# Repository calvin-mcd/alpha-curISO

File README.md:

# Alpha CurISO

The Alpha CurISO is a community pcb for the [Curio](https://mechvault.net/products/group-buy-curio-40-keyboard-kit). It supports two different Alpha Staggers and Ortho Layouts.
This is a collaboration between jade_themaid, airuei, galvy0 and calvin.

## Layout

## Todo

- [ ] order pcb, plates
- [ ] create firmware
- [ ] test pcb in case

## Disclaimer

Please note that this project is a work in progress with no guarantees of a working outcome. No-one involved in this project is responsible for any usage issues that may arise. However, feel free to edit, modify and otherwise utilise these files.

## License

Shield: 

This work is licensed under a  
[Creative Commons Attribution-NonCommercial-ShareAlike 4.0 International License](http://creativecommons.org/licenses/by-nc-sa/4.0/).

## Credits

As always big thanks also to the many people who inspired and helped with this board!

Any questions, contact Calvin0563 on Discord.

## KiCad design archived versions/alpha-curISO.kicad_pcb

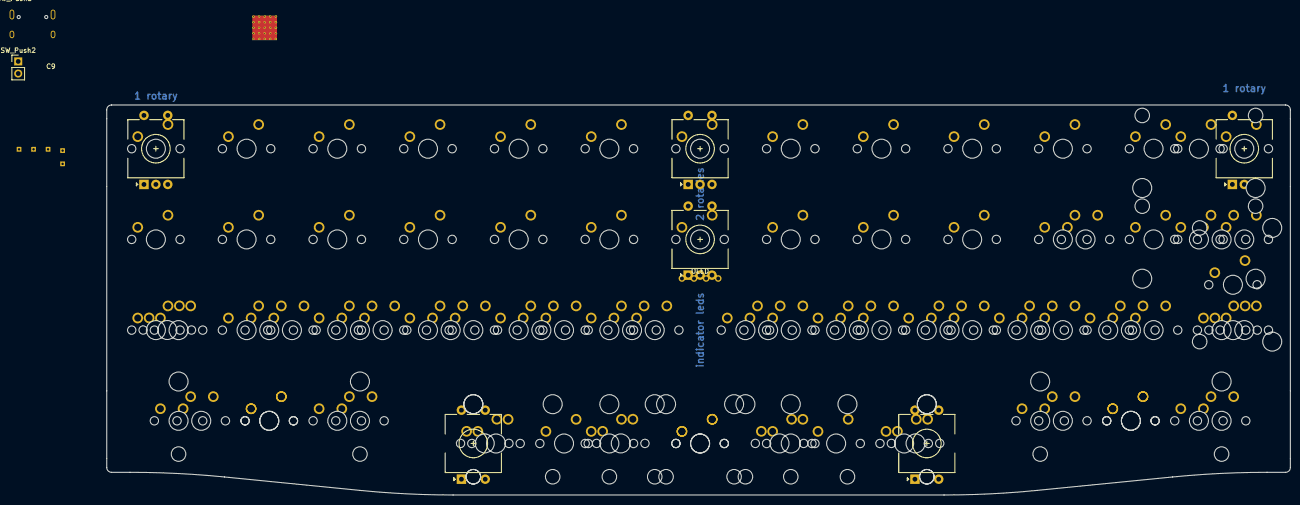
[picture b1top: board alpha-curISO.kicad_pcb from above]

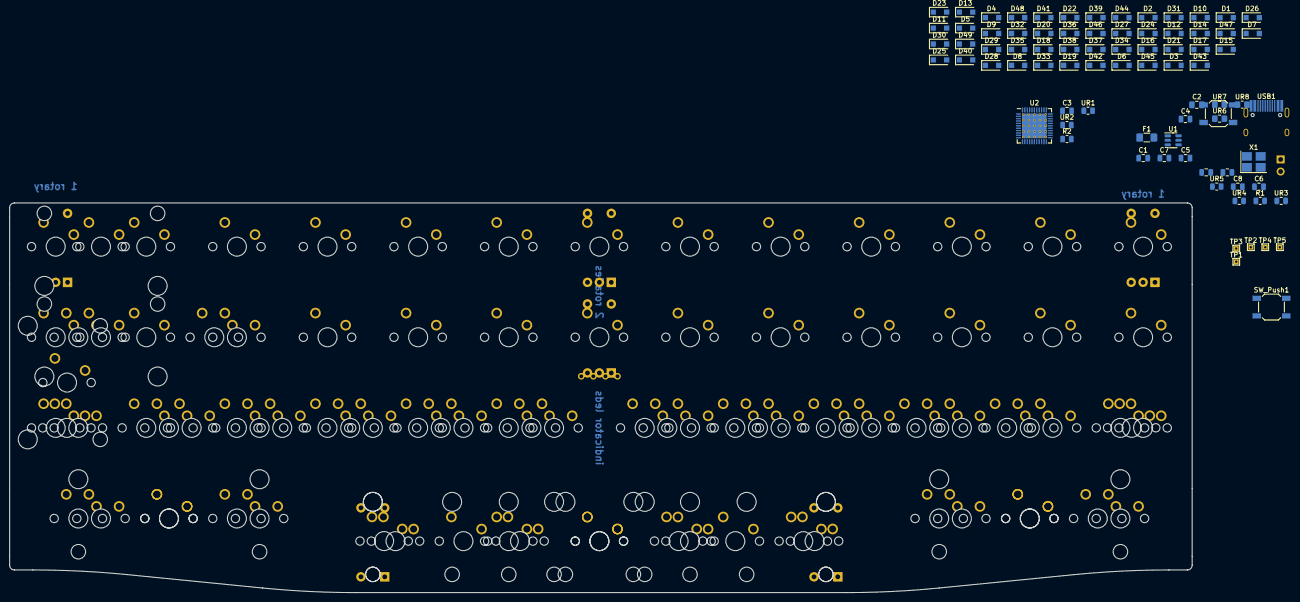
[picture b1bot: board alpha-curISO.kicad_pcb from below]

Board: 2 copper layers, 248.6 x 81.9 mm, 180 parts (81 on the bottom side), 83 nets, no tracks yet.

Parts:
C1: 4.7uF; C_0805_2012Metric
C2: 2.2uF; C_0805_2012Metric_Pad1.18x1.45mm_HandSolder
C3: 1uf; C_0805_2012Metric
C4: 10uF; C_0805_2012Metric
C5, C6, C7, C8: 0.1uf; C_0805_2012Metric
C9, C10: 22p; C_0805_2012Metric
D1, D2, D3, D4, D5, D6, D7, D8, D9, D10, D11, D12, D13, D14, D15, D16, D17, D18, D19, D20, D21, D22, D23, D24, D25, D26, D27, D28, D29, D30, D31, D32, D33, D34, D35, D36, D37, D38, D39, D40, D41, D42, D43, D44, D45, D46, D47, D48, D49: D_Small; D_SOD-123F
F1: Polyfuse_Small; Fuse_1206_3216Metric_Pad1.42x1.75mm_HandSolder
OL1: OLED; OLED_v2
R1, R2: 10k; R_0805_2012Metric
SW1, SW2, SW3, SW4, SW5, SW6, SW7, SW8, SW9, SW10, SW11, SW12, SW13, SW14, SW15, SW16, SW17, SW18, SW19, SW20, SW21, SW22, SW23, SW24, SW25, SW26, SW27(ortho)1, SW28, SW28(1.5stagger)1, SW28(ortho)1, SW29, SW29(1.5stagger)1, SW29(ortho)1, SW30, SW30(1.5stagger)1, SW30(ortho)1, SW31, SW31(1.5stagger)1, SW31(ortho)1, SW32, SW32(1.5stagger)1, SW32(ortho)1, SW33, SW33(1.5stagger)1, SW33(ortho)1, SW34, SW34(1.5stagger)1, SW34(ortho)1, SW35, SW35(1.5stagger)1, SW35(ortho)1, SW36, SW36(1.5stagger)1, SW36(ortho)1, SW37, SW37(1.5stagger)1, SW37(ortho)1, SW38(ortho)1, SW39, SW40, SW41, SW47, SW48, SW49: SW_Push_45deg; MXOnly-1U-NoLED
SW12(2)1, SW26(2)1: SW_Push_45deg; MXOnly-2U-NoLED
SW24(1.5)1, SW25(1.5)1, SW27(1.5)1, SW38(1.5)1, SW39(1.5)1, SW41(1.5)1, SW42(1.5)1, SW46(1.5)1, SW47(1.5)1, SW49(1.5)1: SW_Push_45deg; MXOnly-1.5U-NoLED
SW26(ISO)1: SW_Push_45deg; MXOnly-ISO-NoLED
SW27(1.25)1, SW38(1.25)1, SW42(1.25)1, SW46(1.25)1: SW_Push_45deg; MXOnly-1.25U-NoLED
SW40(3)1, SW42(3)1, SW44(3)1, SW46(3)1, SW48(3)1: SW_Push_45deg; MXOnly-3U-ReversedStabilizers-NoLED
SW43(1.75)1, SW45(1.75)1: SW_Push_45deg; MXOnly-1.75U-NoLED
SW43(2)1, SW45(2)1: SW_Push_45deg; MXOnly-2U-ReversedStabilizers-NoLED
SW44(6)1: SW_Push_45deg; MXOnly-6U-Centered-ReversedStabilizers-NoLED
SW_Push1, SW_Push3: SW_PUSH; SW_SPST_SKQG_WithoutStem
SW_Push2: SW_PUSH; PinHeader_1x02_P2.54mm_Vertical
SW_rotary1, SW_rotary2, SW_rotary3, SW_rotary4, SW_rotary5, SW_rotary6: RotaryEncoder_Switch; RotaryEncoder_EC11-no-legs
TP1: TPGND; TestPoint_THTPad_1.0x1.0mm_Drill0.5mm
TP2: TPVCC; TestPoint_THTPad_1.0x1.0mm_Drill0.5mm
TP3: TPCLK; TestPoint_THTPad_1.0x1.0mm_Drill0.5mm
TP4: TPDATA; TestPoint_THTPad_1.0x1.0mm_Drill0.5mm
TP5: TPRST; TestPoint_THTPad_1.0x1.0mm_Drill0.5mm
U1: SRV05-4; SOT-23-6
U2: ATmega32U4-M; QFN-44-1EP_7x7mm_P0.5mm_EP5.2x5.2mm_ThermalVias
UR1, UR2: 22; R_0805_2012Metric
UR3: 1M; R_0805_2012Metric
UR4, UR5: 5.1k; R_0805_2012Metric
UR6: 100k; R_0805_2012Metric_Pad1.20x1.40mm_HandSolder
UR7, UR8: 4.7k; R_0805_2012Metric_Pad1.20x1.40mm_HandSolder
USB1: HRO-TYPE-C-31-M-12; HRO-TYPE-C-31-M-12-HandSoldering
X1: Crystal_GND24_Small; Crystal_SMD_3225-4Pin_3.2x2.5mm_HandSoldering

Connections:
+5V: C2.1, C4.1, C5.1, C6.1, C7.1, C8.1, F1.2, OL1.3 (VCC), R1.2, TP2.1, U2.2 (UVCC), U2.7 (VBUS), U2.14 (VCC), U2.24 (AVCC), U2.34 (VCC), U2.44 (AVCC), UR7.2, UR8.1
COL0: SW1.1, SW14.1, SW27(1.5)1.1, SW27(1.25)1.1, SW27(ortho)1.1, SW39.1, SW39(1.5)1.1
COL1: SW2.1, SW15.1, SW28.1, SW28(1.5stagger)1.1, SW28(ortho)1.1, SW40.1, SW40(3)1.1
COL2: SW3.1, SW16.1, SW29.1, SW29(1.5stagger)1.1, SW29(ortho)1.1, SW41.1, SW41(1.5)1.1
COL3: SW4.1, SW17.1, SW30.1, SW30(1.5stagger)1.1, SW30(ortho)1.1
COL4: SW5.1, SW18.1, SW31.1, SW31(1.5stagger)1.1, SW31(ortho)1.1, SW42(1.5)1.1, SW42(1.25)1.1, SW42(3)1.1
COL5: SW6.1, SW19.1, SW32.1, SW32(1.5stagger)1.1, SW32(ortho)1.1, SW43(1.75)1.1, SW43(2)1.1
COL6: SW8.1, SW21.1, SW33.1, SW33(1.5stagger)1.1, SW33(ortho)1.1, SW45(1.75)1.1, SW45(2)1.1
COL7: SW9.1, SW22.1, SW34.1, SW34(1.5stagger)1.1, SW34(ortho)1.1, SW46(1.5)1.1, SW46(1.25)1.1, SW46(3)1.1
COL8: SW10.1, SW23.1, SW35.1, SW35(1.5stagger)1.1, SW35(ortho)1.1
COL9: SW11.1, SW24.1, SW24(1.5)1.1, SW36.1, SW36(1.5stagger)1.1, SW36(ortho)1.1, SW47.1, SW47(1.5)1.1
COL11: SW12.1, SW12(2)1.1, SW25.1, SW25(1.5)1.1, SW37.1, SW37(1.5stagger)1.1, SW37(ortho)1.1, SW48.1, SW48(3)1.1
COL12: SW13.1, SW26.1, SW26(2)1.1, SW26(ISO)1.1, SW38(1.5)1.1, SW38(1.25)1.1, SW38(ortho)1.1, SW44(3)1.1, SW44(6)1.1, SW49.1, SW49(1.5)1.1
D+: U1.6 (IO4), UR1.1, USB1.6 (DP1), USB1.8 (DP2)
D-: U1.1 (IO1), UR2.1, USB1.5 (DN2), USB1.7 (DN1)
GND: C1.1, C3.2, C4.2, C5.2, C6.2, C7.2, C8.2, C9.2, C10.2, OL1.4 (GND), R2.1, SW_Push1.1, SW_Push2.1, SW_Push3.1, TP1.1, U1.2 (VN), U2.5 (UGND), U2.15 (GND), U2.23 (GND), U2.35 (GND), U2.43 (GND), U2.45 (GND), UR3.2, UR4.2, UR5.2, UR6.2, USB1.1 (GND), USB1.12 (GND), X1.2, X1.4
unnamed: C1.2, UR3.1, USB1.13 (SHIELD)
unnamed: C2.2, TP5.1, UR6.1
unnamed: C3.1, U2.6 (UCAP)
unnamed: D2.2 (A), SW14.2
unnamed: D3.2 (A), SW27(1.5)1.2, SW27(1.25)1.2, SW27(ortho)1.2
unnamed: D4.2 (A), SW39.2, SW39(1.5)1.2
unnamed: D5.2 (A), SW2.2
unnamed: D6.2 (A), SW15.2
unnamed: D7.2 (A), SW28.2, SW28(1.5stagger)1.2, SW28(ortho)1.2
unnamed: D8.2 (A), SW40.2, SW40(3)1.2
unnamed: D9.2 (A), SW3.2
unnamed: D10.2 (A), SW16.2
unnamed: D11.2 (A), SW29.2, SW29(1.5stagger)1.2, SW29(ortho)1.2
unnamed: D12.2 (A), SW41.2, SW41(1.5)1.2
unnamed: D13.2 (A), SW4.2
unnamed: D14.2 (A), SW17.2
unnamed: D15.2 (A), SW30.2, SW30(1.5stagger)1.2, SW30(ortho)1.2
unnamed: D16.2 (A), SW5.2
unnamed: D17.2 (A), SW18.2
unnamed: D18.2 (A), SW31.2, SW31(1.5stagger)1.2, SW31(ortho)1.2
unnamed: D20.2 (A), SW6.2
unnamed: D21.2 (A), SW19.2
unnamed: D22.2 (A), SW32.2, SW32(1.5stagger)1.2, SW32(ortho)1.2
unnamed: D23.2 (A), SW43(1.75)1.2, SW43(2)1.2
unnamed: D24.2 (A), SW44(3)1.2, SW44(6)1.2
unnamed: D27.2 (A), SW8.2
unnamed: D28.2 (A), SW21.2
unnamed: D29.2 (A), SW33.2, SW33(1.5stagger)1.2, SW33(ortho)1.2
unnamed: D30.2 (A), SW45(1.75)1.2, SW45(2)1.2
unnamed: D31.2 (A), SW9.2
unnamed: D32.2 (A), SW22.2
unnamed: D33.2 (A), SW34.2, SW34(1.5stagger)1.2, SW34(ortho)1.2
unnamed: D35.2 (A), SW10.2
unnamed: D36.2 (A), SW23.2
unnamed: D37.2 (A), SW35.2, SW35(1.5stagger)1.2, SW35(ortho)1.2
unnamed: D38.2 (A), SW11.2
unnamed: D39.2 (A), SW24.2, SW24(1.5)1.2
unnamed: D40.2 (A), SW36.2, SW36(1.5stagger)1.2, SW36(ortho)1.2
unnamed: D41.2 (A), SW47.2, SW47(1.5)1.2
unnamed: D42.2 (A), SW12.2, SW12(2)1.2
unnamed: D43.2 (A), SW25.2, SW25(1.5)1.2
unnamed: D44.2 (A), SW37.2, SW37(1.5stagger)1.2, SW37(ortho)1.2
unnamed: D45.2 (A), SW48.2, SW48(3)1.2
unnamed: D47.2 (A), SW26.2, SW26(2)1.2, SW26(ISO)1.2
unnamed: D48.2 (A), SW38(1.5)1.2, SW38(1.25)1.2, SW38(ortho)1.2
unnamed: D49.2 (A), SW49.2, SW49(1.5)1.2
unnamed: R2.2, U2.33 (~HWB/PE2)
unnamed: U2.3 (D-), UR2.2
unnamed: U2.4 (D+), UR1.2
unnamed: UR4.1, USB1.4 (CC1)
unnamed: UR5.1, USB1.10 (CC2)
PD2: TP4.1, UR7.1
PD5: TP3.1, UR8.2
ROW0: D1.1 (K), D5.1 (K), D9.1 (K), D13.1 (K), D16.1 (K), D20.1 (K), D25.1 (K), D27.1 (K), D31.1 (K), D35.1 (K), D38.1 (K), D42.1 (K), D46.1 (K)
ROW1: D2.1 (K), D6.1 (K), D10.1 (K), D14.1 (K), D17.1 (K), D21.1 (K), D26.1 (K), D28.1 (K), D32.1 (K), D36.1 (K), D39.1 (K), D43.1 (K), D47.1 (K)
ROW2: D3.1 (K), D7.1 (K), D11.1 (K), D15.1 (K), D18.1 (K), D22.1 (K), D29.1 (K), D33.1 (K), D37.1 (K), D40.1 (K), D44.1 (K), D48.1 (K)
ROW3: D4.1 (K), D8.1 (K), D12.1 (K), D19.1 (K), D23.1 (K), D24.1 (K), D30.1 (K), D34.1 (K), D41.1 (K), D45.1 (K), D49.1 (K)
RST: R1.1, SW_Push1.2, SW_Push2.2, SW_Push3.2, U2.13 (~RESET)
R_row1: D1.2 (A), SW1.2
R_row2: D46.2 (A), SW13.2
R_row3: D25.2 (A), SW7.2
R_row4: D26.2 (A), SW20.2
R_row5: D19.2 (A), SW42(1.5)1.2, SW42(1.25)1.2, SW42(3)1.2
R_row6: D34.2 (A), SW46(1.5)1.2, SW46(1.25)1.2, SW46(3)1.2
VCC: F1.1, U1.5 (VP), USB1.2 (VBUS), USB1.11 (VBUS)
XTAL1: C9.1, U2.17 (XTAL1), X1.1
XTAL2: C10.1, U2.16 (XTAL2), X1.3

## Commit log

2023-01-24 start kicad project
2023-01-25 initialise
2023-01-26 add components to schematic
2023-01-26 split schematics
2023-01-27 edited schematics, assigned footprints
    4u spacebar missing, no appropriate footprint in library yet
2023-01-28 footprint WIP
2023-01-28 arrange footprints
2023-01-28 calvin's work
2023-01-28 update schematic
2023-01-28 rp2040 pcb file and schematic created
    MCU & USB component placement
    early matrix routing
2023-01-30 new position
2023-01-30 MCU routing, RGB leds
    MCU first routing draft finished
    added RGB leds instead of diodes
2023-01-30 adding library for underglow rgbs
2023-01-31 changed MCU placement, redid routing
2023-01-31 added underglow to schematics
2023-01-31 galvy edits - start routing testing
2023-01-31 quick look, noticed a stab contact interference
2023-02-01 rgb underglow footprints placed
2023-02-01 encoder, plate
2023-02-01 first bunch of routing
2023-02-01 finished first rough routing
    short 1 pin
    some GND are not connected to the GND layer
2023-02-02 first full routing
    no error check, not very clean routing
2023-02-03 corrected schematic component value
2023-02-03 production files created
2023-02-03 added RGB components for 5v / 3v3 voltage regulation
2023-02-04 tiny schematics clean up
2023-02-04 rgb schematics
2023-02-04 rgb fixed, rotaries separately reconnected
2023-02-04 shifter symbol edited
2023-02-06 speaker added, sharing pin with bottom left rotary
2023-02-11 routing cleanup, first DRC
    added a bunch of errors to DRC, should be fine but good to double check
2023-02-11 more tweaks
2023-02-11 further tweaks
2023-02-11 tweaks
2023-02-13 attempt at rerouting
2023-02-15 start new placement
2023-02-22 added routing version that i worked on in kicad6
2023-02-23 symmetry work
2023-02-24 finished new PCB draft
    ran preliminary DRC
    cleaned up project folder
2023-02-24 cleanup folder
2023-02-24 created SVGs for custom hatched fill
2023-02-25 catching up with the progress made in 7
    catching up work, setting up pcb for round traces, and octagonal pads if desired
    implemented complex speakers
2023-02-26 fixed mistakes in schematics to footprints
2023-02-27 finished prototype pcb
    missing silkscreen, production files
    needs clarification of some errors
2023-02-27 production files, svgs
2023-02-27 changed nets a bit
2023-03-03 archived unused project files in kicad 6 wip branch
2023-03-05 proudction files
2023-03-16 added reset button
2023-03-20 added iso 1.5 key option, new production files
2023-03-25 production files
2023-04-13 backup
2023-04-14 changed led alignment&distance to be more uniform
2023-04-15 clean up of routing and other small details
2023-04-15 simplified speaker mechanic
2023-04-17 added 4 more leds for underglow
2023-04-17 routing cleaning
2023-04-18 added capacitors for each led, some routing tweaks
2023-04-18 caps and routing
2023-04-18 tiny tweak
2023-04-18 small tweaks
2023-04-20 oled changed to 3v3
2023-04-20 trackpoint changed to 3v3
2023-05-15 bottom row routing clean up
2023-05-21 bom pos
2023-06-13 small routing changes, 5V circuit closed
2023-08-01 labelling of KLE options
2023-08-01 small routing change
2023-08-02 cleaning up main folder
2023-08-02 deleting older versions
2023-08-02 fresh svgs, small routing changes
2023-08-05 routing update
2023-08-16 slight backsilkscreen improvement
2023-09-20 moved project to kicad 7
2023-09-25 updated 2020 symbols and routing
2023-09-25 added plate project for breakoff
2023-09-29 plate work
2023-09-29 updated silkscreen elements
    removed all previous graphics and added curiso logo, credits + personal logos, gear flower pattern, kurisu peek on front; big kurisu on back
2023-10-15 Added .png of plate
    Exported a .png of the Alpha CurISO plate in the same directory as the plate files
2023-11-11 Converted circle pads to octagon pads
    Used Oktizer action plugin to convert cirlce pads to octagonal pads so that the pads are more in-line with the "gear" theme of the silkscreen
2023-11-17 error checked
2023-11-19 Added prototype badge on silkscreen
2023-11-20 fresh production files
2024-03-30 updating project
